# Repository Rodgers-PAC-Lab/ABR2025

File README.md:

# ABR2025

## Introduction

This repository contains code to implement the ABR measuring system described
in Gargiullo et al, as well as the analysis scripts needed to replicate the 
figures in that paper.
Preprint: https://www.biorxiv.org/content/10.64898/2025.12.17.694771v1

The repository is structured as follows:
- `./` - The toplevel directory, containing this README file
- `./designs` - Design files, bill of materials, and other information about 
physically building the system.
- `./src` - source code for analysis and GUI. Import like `import opensabr`
- `./src/gui` - A Python module for running the graphical user interface (GUI) 
to take ABR data. It can be imported like `import opensabr.gui`. This code is 
run on a desktop PC connected to the ABR measuring system hardware.
- `./scripts` - A folder of demo scripts that generate the figures in the
paper, using data that we collected and have shared on Zenodo. These scripts 
are meant to be run one at a time, not imported and called by other scripts. 

## Requirements

We used Python 3.11. Newer versions may also work but we did not test them.

requirements-lock.txt includes the exact versions we used

For the analysis scripts (but not the GUI), the following repository is 
required. It should be on your PYTHONPATH so that it can be imported using
the syntax `import my`.
- `git clone git@github.com:Rodgers-PAC-Lab/my.git`

TODO: only my.plot is needed, bring minimal into this repo

## Instructions

To build the hardware, refer to the file `./designs/README`. 

To run the GUI and measure ABR, refer to the file `./gui/README`.

To run the analysis scripts and regenerate the figures included in the paper,
refer to the file `./scripts/README`.

## Overall installation instructions
These instructions walk you through the installation of OpenSABR, our fork
of ABRA, and our fork of ABRpresto in three different conda environments.
If you only want to run OpenSABR, you can skip the other two environments --
they are only used to provide a point of comparison in the paper. 

We clone repositories that are installed using a method like `pip install`
into a directory called `~/dev/installed`. We clone repositories that are 
not installable, but need to be imported, into a directory called `~/dev`.
ABRA is the only one that must be cloned into `~/dev`.
This is because it can cause errors to mix these two kinds of repositories.
`~/dev` must be on the PYTHONPATH for this to work. 

For ABRA, we recommend the CPU packages, there is no need for GPU.

The three conda environments share data written to disk in the parquet format.

## Installing OpenSABR
# Clone repo
cd ~/installed
git clone git@github.com:Rodgers-PAC-Lab/OpenSABR
cd OpenSABR

# --- Install: pick ONE of Option A or Option B ---

# Option A: Typical install (no version pins)
conda create -n opensabr -c conda-forge python=3.11 pip ipython
conda activate opensabr
conda install -c conda-forge numpy scipy pandas matplotlib tqdm pyqt pyqtgraph pyserial pyarrow seaborn
pip install -e . --no-deps

# Option B: Reproducible install from lock (linux-64 only)
conda create -n opensabr --file opensabr-conda-lock.txt
conda activate opensabr
pip install -e . --no-deps

## Installing ABRpresto
# Clone repo
cd ~/installed 
git clone git@github.com:Rodgers-PAC-Lab/ABRpresto # our fork
cd ABRpresto
git checkout dev # our branch with fixes

# --- Install: pick ONE of Option A or Option B ---

# Option A: Typical install (no version pins)
conda create -n abrpresto -c conda-forge python=3.11 ipython pip
conda activate abrpresto
conda install -c conda-forge numpy scipy pandas matplotlib setuptools_scm pyarrow tqdm
pip install -e . --no-deps

# Option B: Reproducible install from lock (linux-64 only)
conda create -n abrpresto --file abrpresto-conda-lock.txt
conda activate abrpresto
pip install -e . --no-deps

## Installing ABRA
# Clone repo (must be under ~/dev or some location on PYTHONPATH)
cd ~/dev
git clone git@github.com:Rodgers-PAC-Lab/abranalysis # our fork
cd abranalysis
git checkout dev # our branch with fixes

# --- Install: pick ONE of Option A or Option B ---
# ABRA cannot be pip-installed; it is imported via PYTHONPATH in both options.

# Option A: Typical install (no version pins)
conda create -n abra -c conda-forge python=3.11 ipython pip
conda activate abra
conda install -c conda-forge numpy scipy pandas scikit-learn pytorch=*=cpu* keras tensorflow streamlit easydict "altair<5" pyarrow matplotlib tqdm
conda env config vars set PYTHONPATH=$HOME/dev
conda deactivate && conda activate abra   # reload so PYTHONPATH takes effect

# Option B: Reproducible install from lock (linux-64 only)
conda create -n abra --file abra-conda-lock.txt
conda activate abra
conda env config vars set PYTHONPATH=$HOME/dev
conda deactivate && conda activate abra   # reload so PYTHONPATH takes effect

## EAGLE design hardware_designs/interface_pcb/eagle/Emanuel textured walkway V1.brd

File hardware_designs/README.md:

# ABR2025 - hardware designs

## Introduction 

This folder contains the designs needed to build the hardware for the 
ABR measuring system described in Gargiullo 2025.

It contains the following subfolders:
- bill_of_materials.xlsx: Bill of Materials for all required parts
- interface_pcb/: PCB design files for the "interface PCB" that houses the
Teensy and connects to the other boards
- teensy/: Files for the code that runs on the Teensy

### Bill of Materials

This is an Excel file of all required components. You will also need standard
electronics equipment for soldering, etc.

### Interface PCB

This PCB was designed in Eagle. The original design files are located in the
`eagle` subdirectory and can be opened in the Eagle software. You only need to 
do this if you want to edit the PCB.

If you just want to print the PCB, use the files in the `gerbers` subdirectory.
These are the standard manufacturing format that all PCB printing companies use.
We used OSH Park to print the PCB.

After you receive the PCB, you will need to populate a few components. Details
are available in the "Supplemental Material", which also explains how to 
physically assemble all components.

### Teensy files

This is the software that runs on the Teensy. The software controls the 
ADS1299, and it also interfaces with the desktop computer running the GUI
(see `../gui/README`). Flash the files included here on the Teensy.

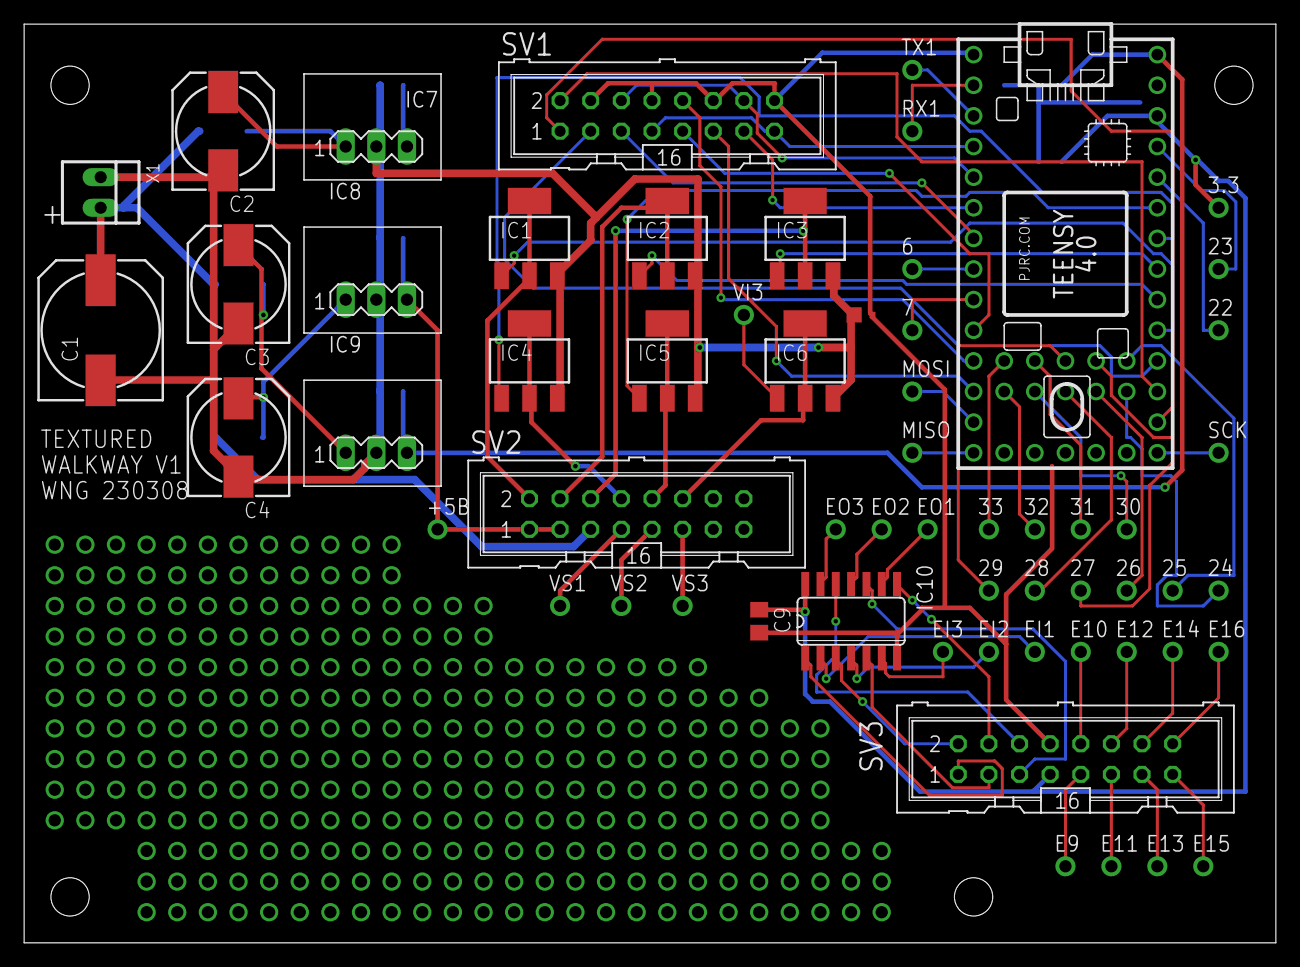
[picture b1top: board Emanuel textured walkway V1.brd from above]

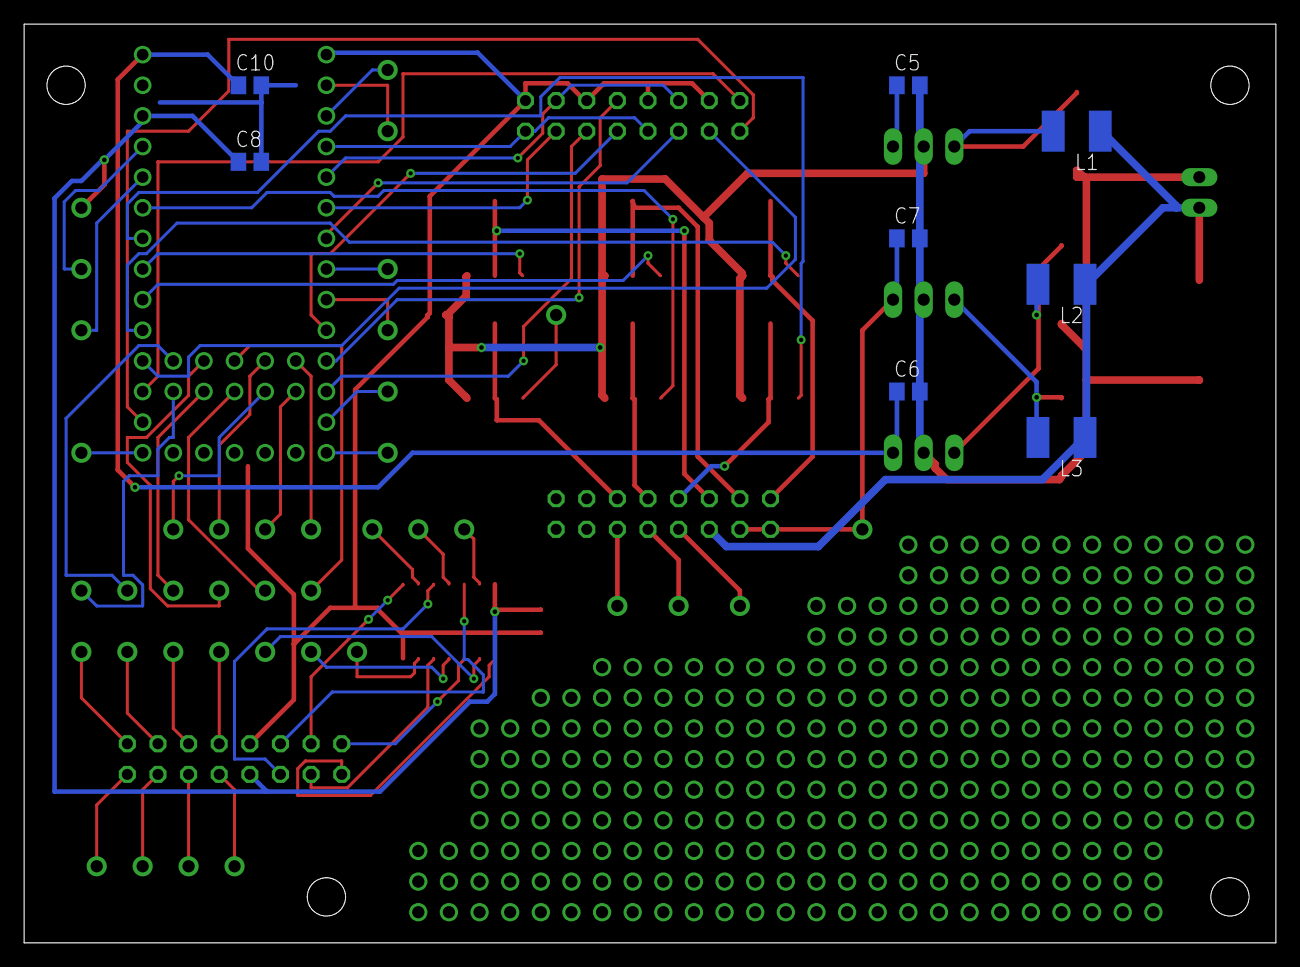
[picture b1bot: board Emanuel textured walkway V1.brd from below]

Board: 2 copper layers, 103.8 x 76.2 mm, 68 parts (8 on the bottom side), 74 nets.

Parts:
3.3: 3.3; P1-040-100
6, 7, 22, 23, 24, 25, 26, 27, 28, 29, 30, 31, 32, 33: TP-040-100; P1-040-100
+5B: TP-040-100; P1-040-100
C1: 330/35; 140CLH-1010
C2, C3, C4: 100/35; 140CLH-0810
C5, C6, C7: 1uF; C0805
C8, C9, C10: 100nF; C0805
E9, E10, E11, E12, E13, E14, E15, E16: TP-040-100; P1-040-100
EI1, EI2, EI3: TP-040-100; P1-040-100
EO1, EO2, EO3: TP-040-100; P1-040-100
IC1, IC2, IC3, IC4, IC5, IC6: BTS3118N; SOT223
IC7: 78E-12V; RECOM-R-78E
IC8, IC9: 78E-5V; RECOM-R-78E
IC10: 74LS14D; SO14
J1: TRCV-175-LARGE; JUMPER-TRACE-CONVERT-LARGER-PADS-175
L1, L2, L3: 10uH; L1812
MISO: TP-040-100; P1-040-100
MOSI: TP-040-100; P1-040-100
RX1: TP-040-100; P1-040-100
SCK: TP-040-100; P1-040-100
SV1: STEPPER; ML16
SV2: I/O-1; ML16
SV3: EXTRA; ML16
TX1: TP-040-100; P1-040-100
U$1: TEENSY_4.0_WITH_24-33
VI3: TP-040-100; P1-040-100
VS1, VS2, VS3: TP-040-100; P1-040-100
X1: 22-23-2021

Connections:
+3.3V: 3.3.P$1, C8.1, C9.1, IC10.14, SV3.7, U$1.3V3_LO
+5B: +5B.P$1, C7.1, IC8.3, SV2.1, SV2.3
+5V: C6.1, C10.1, IC9.3, U$1.VIN
+12V: C5.1, IC7.3
+24V: C1.+, L1.1, L2.1, L3.1, SV2.5, X1.2
DIR: SV1.7, SV1.15, U$1.2
EN1: SV1.13, U$1.4
EN2: SV1.5, U$1.5
GND: C8.2, C9.2, C10.2, IC10.7, J1.2S, SV1.4, SV1.8, SV1.12, SV1.16, SV3.8, U$1.GND, U$1.GND2, U$1.GND3
IN1-1: SV1.9, U$1.8
IN1-2: SV1.10, U$1.9
IN1-3: SV1.11, U$1.10/CS
IN2-1: SV1.1, U$1.14/A0
IN2-2: SV1.2, U$1.15/A1
IN2-3: SV1.3, U$1.16/A2
M1: IC3.2, IC3.4, SV2.6
MAGNETS: IC3.1, U$1.19/A5/SCL
unnamed: C2.+, IC7.1, L1.2
unnamed: C4.+, IC8.1, L3.2
unnamed: SV2.9, VS2.P$1
unnamed: SV2.11, VS3.P$1
unnamed: C3.+, IC9.1, L2.2
unnamed: IC6.1, VI3.P$1
unnamed: MOSI.P$1, U$1.11/MOSI
unnamed: MISO.P$1, U$1.12/MISO
unnamed: SV2.7, VS1.P$1
unnamed: SCK.P$1, U$1.13/SCK
unnamed: 22.P$1, U$1.22/A8
unnamed: 23.P$1, U$1.23/A9
unnamed: 24.P$1, U$1.24
unnamed: 33.P$1, U$1.33
unnamed: 32.P$1, U$1.32
unnamed: 31.P$1, U$1.31
unnamed: 30.P$1, U$1.30
unnamed: 29.P$1, U$1.29
unnamed: 28.P$1, U$1.28
unnamed: 27.P$1, U$1.27
unnamed: 26.P$1, U$1.26
unnamed: 25.P$1, U$1.25
unnamed: RX1.P$1, U$1.0/RX
unnamed: TX1.P$1, U$1.1/TX
unnamed: 6.P$1, U$1.6
unnamed: 7.P$1, U$1.7
unnamed: IC10.1, SV3.1
unnamed: IC10.3, SV3.2
unnamed: IC10.5, SV3.3
unnamed: IC10.8, SV3.4
unnamed: IC10.10, SV3.5
unnamed: IC10.12, SV3.6
unnamed: E9.P$1, SV3.9
unnamed: E11.P$1, SV3.11
unnamed: E13.P$1, SV3.13
unnamed: E15.P$1, SV3.15
unnamed: E10.P$1, SV3.10
unnamed: E12.P$1, SV3.12
unnamed: E14.P$1, SV3.14
unnamed: E16.P$1, SV3.16
unnamed: EI1.P$1, IC10.2
unnamed: EI3.P$1, IC10.6
unnamed: EI2.P$1, IC10.4
unnamed: EO3.P$1, IC10.13
unnamed: EO1.P$1, IC10.9
unnamed: EO2.P$1, IC10.11
PGND: C1.-, C2.-, C3.-, C4.-, C5.2, C6.2, C7.2, IC1.3, IC2.3, IC3.3, IC4.3, IC5.3, IC6.3, IC7.2, IC8.2, IC9.2, J1.1L, X1.1
SO1: IC4.2, IC4.4, SV2.8
SO2: IC5.2, IC5.4, SV2.10
SO3: IC6.2, IC6.4, SV2.12
SPARE-OUT1: IC4.1, U$1.20/A6
SPARE-OUT2: IC5.1, U$1.21/A7
STEP: SV1.6, SV1.14, U$1.3
V1: IC1.2, IC1.4, SV2.2
V2: IC2.2, IC2.4, SV2.4
VALVE1: IC1.1, U$1.17/A3
VALVE2: IC2.1, U$1.18/A4/SDA

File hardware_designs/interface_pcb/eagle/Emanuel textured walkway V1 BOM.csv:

Partlist exported from C:/Users/Bill/Dropbox/EAGLE/projects/
Alan Emanuel textured walkway/Emanuel textured walkway V1.sch at 4/9/2025 10:39 AM


Qty 	Value	                 Device	                Parts                                                                                                                                                                        
3   	1uF                   	C-USC0805             	C5, C6, C7                                                                                                                                                                   
1   	3.3                   	TP-040-100            	3.3                                                                                                                                                                          
3   	10uH                  	L-USL1812             	L1, L2, L3                                                                                                                                                                   
1   	22-23-2021            	22-23-2021            	X1                                                                                                                                                                           
1   	74LS14D               	74LS14D               	IC10                                                                                                                                                                         
2   	78E-5V                	RECOM-R-78E           	IC8, IC9                                                                                                                                                                     
1   	78E-12V               	RECOM-R-78E           	IC7                                                                                                                                                                          
3   	100/35                	CPOL-US140CLH-0810    	C2, C3, C4                                                                                                                                                                   
3   	100nF                 	C-USC0805             	C8, C9, C10                                                                                                                                                                  
1   	330/35                	CPOL-US140CLH-1010    	C1                                                                                                                                                                           
6   	BTS3118N              	BTS3118N              	IC1, IC2, IC3, IC4, IC5, IC6                                                                                                                                                 
1   	EXTRA                 	ML16                  	SV3                                                                                                                                                                          
1   	I/O-1                 	ML16                  	SV2                                                                                                                                                                          
1   	STEPPER               	ML16                  	SV1                                                                                                                                                                          
1   	TEENSY_4.0_WITH_24-33 	TEENSY_4.0_WITH_24-33 	U$1                                                                                                                                                                          
38  	TP-040-100            	TP-040-100            	+5B, 6, 7, 22, 23, 24, 25, 26, 27, 28, 29, 30, 31, 32, 33, E9, E10, E11, E12, E13, E14, E15, E16, EI1, EI2, EI3, EO1, EO2, EO3, MISO, MOSI, RX1, SCK, TX1, VI3, VS1, VS2, VS3
1   	TRCV-175-LARGE        	TRCV-175-LARGE        	J1

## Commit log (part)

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2025-07-21 Starting to copy stuff over to the new repo. Also changed the get_filepaths() function to take a json with filepaths as discussed.
2025-07-22 deleting abr subfolder
2025-07-22 move analysis scripts into main directory
2025-07-22 add metadata mouse_info.csv
2025-07-22 explain how to set up filepaths.json
2025-07-22 add filepaths.json to gitignore
2025-07-22 newline added
2025-07-22 load from filepaths and mouse_data.csv in current directory
2025-07-22 import abr from paclab
2025-07-22 fix directory names
2025-07-22 Possible solution to the whole two mouse_info.csv thing. Add cohort name to the filename and have both in there, use RUN_STEPS1-2 to do the first two steps to both cohorts. You'll want to run Step3 i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
2025-07-23 CR versions to avoid merge conflict
2025-07-24 remove slow code and update filename
2025-07-24 doc and remove ion
2025-07-24 doc; remove ion; update filepaths
2025-07-24 add Rowan's stats_pickle_v2
2025-07-24 update filepaths and doc
2025-07-24 adding rowan's Grand_averages
2025-07-24 update filepaths
2025-07-24 Changes we made together
2025-07-24 Forgot to add these earlier
2025-07-25 doc and spacing
2025-07-25 split Step2 into Step2 and Step2b
2025-07-25 spacing; doc; save data
2025-07-25 update - new way of parsing, new types of csv
2025-07-25 rename
2025-07-25 remove include drop (done in Step1 now)
2025-07-25 new csv
2025-07-25 move savefils
2025-07-28 move thresh to Step2c; add figs for Step2b
2025-07-28 stub for EKG
2025-07-28 PSD plotting script
2025-07-29 EKG plots
2025-08-10 remove RUN_STEPS1-2
2025-08-11 plots and update for step2b
2025-08-12 fix the noise plot
2025-08-12 deleting old file; renaming grand_averages to step3a
2025-08-12 psd plot
2025-08-12 correlate
2025-08-13 remove
2025-08-13 remove old files
2025-08-15 remove fig4_plots
2025-08-18 remove Plot_thresholds
2025-08-18 add metadata to subdirectory
2025-08-18 move metadata to subfolder
2025-08-18 savefig
2025-08-19 update doc about which scripts make which plots
2025-08-20 Metadata csvs are in a subfolder, changed the hard coded file path to reflect that.
2025-08-21 Renamed scripts
2025-08-23 add 250725_cohort to metadata
2025-08-23 make figures dir
2025-08-23 fix dB; check for glitches on load
2025-08-23 store figs in figures
2025-08-23 fix loudest db and store figs in figures
2025-08-23 another bad session
2025-08-23 show
2025-08-24 error bars for plot_abr_rms
2025-08-24 store all figures in figures/
2025-08-24 remove torn data
2025-08-24 doc; store Pxx; correct stats
2025-08-24 fix aggregation
2025-08-24 fix loudest_db; update
2025-08-24 handle missing mice
2025-08-24 remove breakpoint
2025-08-24 drop more torn sessions
2025-08-24 properly label channels
2025-08-24 update figures
2025-09-01 stats
2025-10-28 indenting
2025-10-28 comment
2025-10-29 also get PSDs
2025-10-29 just plot PSD
2025-10-29 plot raw data script
2025-10-30 also get EKG
2025-10-30 adjust for EKG loaded in Step2a1 now
2025-11-02 todo
2025-11-23 move everything for the paper into scripts
2025-11-23 Revert "move everything for the paper into scripts"
    This reverts commit 5d96bef88c4e92456698c6ead33062e73cff930a.
2025-11-23 Reapply "move everything for the paper into scripts"
    This reverts commit 08afd14b9bcfc3f12d41770581b7fc40990b161a.
2025-11-23 add gui files
2025-11-23 add loading and signal processing
2025-11-23 make it a module
2025-11-23 ignore scripts/figures
2025-11-23 do HL_type right away; replace module name; mice are now dropped upstream
2025-11-23 fix module name; slice more data
2025-11-23 remove imports, fix echoing
2025-11-23 remove imports; fix modulename
2025-11-23 return to typical window size
2025-11-23 replace module names
2025-11-23 fix font
2025-11-23 save aggregated versions in Step2b
2025-11-23 module fix; use none instead of nan; some stuff done upstream
2025-11-23 mice now dropped upstream
2025-11-23 fix bug
2025-11-23 remove dup code now upstream
2025-11-23 move aggregation upstream and always do first experiment
2025-11-23 remove doc
2025-11-26 update calibration
2025-11-26 code to check psd by sex and HL
2025-11-26 adjust for SPL
2025-11-26 fix SPL; stats on threshold; stub code on rms comparisons
2025-11-26 removing old code
2025-11-26 doc on stats; fix mu
2025-12-06 ignore pycache
2025-12-07 fix missing join on trial_counts
2025-12-07 fix colorbar and update doc
2025-12-07 fix colorbar an dyticks
2025-12-09 update peak height analysis
2025-12-11 dump overall N
2025-12-11 more stats
2025-12-12 PCB files
2025-12-12 removing old style paclab.abr imports
2025-12-12 bring in the old functions for identifying onsets
2025-12-12 move psd to signal_processing
2025-12-13 rewrite to generate CSV files and to use sliced dataset
2025-12-13 use new CSV metadata and new sliced dataset
2025-12-14 fix ticks
2025-12-14 move get_ABR_data_paths to paclab.abr_misc
2025-12-14 move old functios to abr_misc
2025-12-14 doc on zip
2025-12-14 READMEs
2025-12-14 adding teensy file
2025-12-14 updating readme
2025-12-15 moved teensy and renamed designs
2025-12-15 Added bill of materials
2025-12-15 Add download link for ABR data in README
2025-12-15 Adding teensy .cpp and .h files
2025-12-18 remove now unnecessary Step1
2026-03-18 fix legend order
2026-06-24 create output dir
2026-06-24 missing space
2026-06-24 begin inverting channels; remove old commented code
2026-06-24 add PLOT_GROWTH_FUNCTIONS
2026-06-24 invert channels
2026-06-29 align yaxis across plots
2026-06-30 invert
2026-06-30 add plot vs age
